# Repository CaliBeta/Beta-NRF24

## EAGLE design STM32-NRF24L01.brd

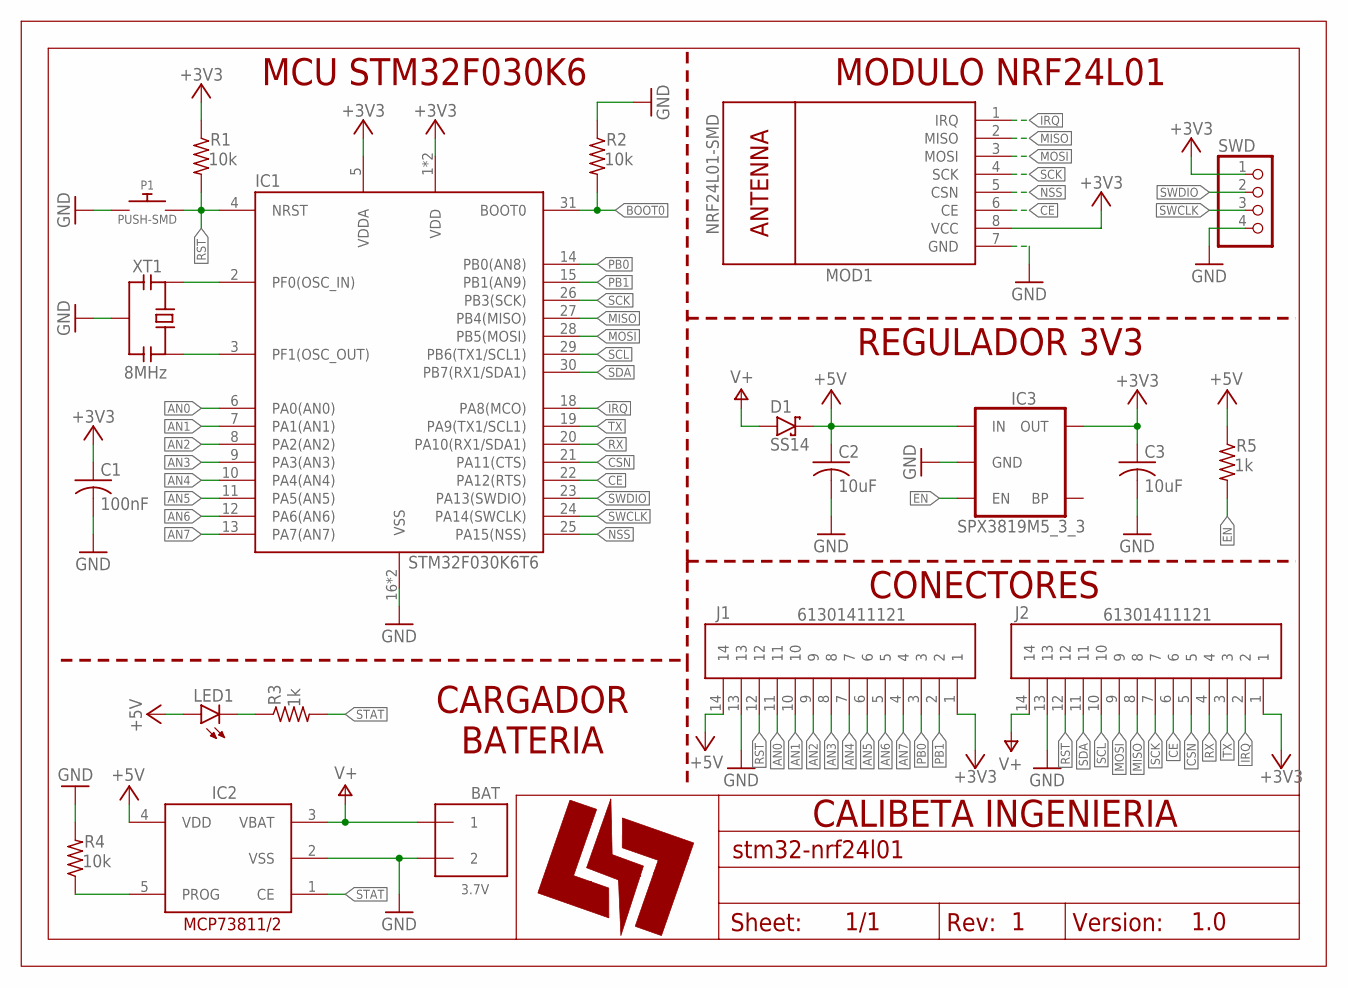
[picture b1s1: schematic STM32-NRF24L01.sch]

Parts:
BAT: 3.7V; S2B-PH-SM4
C1: 100nF; C0805
C2, C3: 10uF; C0805
D1: SS14; DO-214AC
IC1: STM32F030K6T6; LQFP32
IC2: MCP73811/2; SOT23-5L
IC3: SPX3819M5_3_3; SOT23-5
J1, J2: 61301411121
LED1: LED-ROJO0805; LED0805-ROJO
MOD1: NRF24L01-SMD
P1: PUSH-SMD; ST-SMD-6X3.5MM
R1, R2, R4: 10k; R0805
R3, R5: 1k; R0805
SWD: PINHD-1X4/90; 1X04/90
U$1: A5_H-LOGO; LOGO-10MM
XT1: 8MHz; 3-SMD

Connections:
+3V3: C1.1, C3.1, IC1.1 (VDD), IC1.5 (VDDA), IC1.17 (VDD), IC3.5 (OUT), J1.1, J2.1, MOD1.8 (VCC), R1.1, SWD.1
+5V: C2.1, D1.K, IC2.4 (VDD), IC3.1 (IN), J1.14, LED1.A, R5.1
AN0: IC1.6 (PA0(AN0)), J1.11
AN1: IC1.7 (PA1(AN1)), J1.10
AN2: IC1.8 (PA2(AN2)), J1.9
AN3: IC1.9 (PA3(AN3)), J1.8
AN4: IC1.10 (PA4(AN4)), J1.7
AN5: IC1.11 (PA5(AN5)), J1.6
AN6: IC1.12 (PA6(AN6)), J1.5
AN7: IC1.13 (PA7(AN7)), J1.4
BOOT0: IC1.31 (BOOT0), R2.2
CE: IC1.22 (PA12(RTS)), J2.6, MOD1.6 (CE)
CSN: IC1.21 (PA11(CTS)), J2.5
EN: IC3.3 (EN), R5.2
GND: BAT.2, C1.2, C2.2, C3.2, IC1.16 (VSS), IC1.32 (VSS), IC2.2 (VSS), IC3.2 (GND), J1.13, J2.13, MOD1.7 (GND), P1.1, R2.1, R4.2, SWD.4, XT1.2 (GND)
IRQ: IC1.18 (PA8(MCO)), J2.2, MOD1.1 (IRQ)
MISO: IC1.27 (PB4(MISO)), J2.8, MOD1.2 (MISO)
MOSI: IC1.28 (PB5(MOSI)), J2.9, MOD1.3 (MOSI)
unnamed: IC1.2 (PF0(OSC_IN)), XT1.1 (X1)
unnamed: IC1.3 (PF1(OSC_OUT)), XT1.3 (X2)
unnamed: LED1.C, R3.1
unnamed: IC2.5 (PROG), R4.1
NSS: IC1.25 (PA15(NSS)), MOD1.5 (CSN)
PB0: IC1.14 (PB0(AN8)), J1.3
PB1: IC1.15 (PB1(AN9)), J1.2
RST: IC1.4 (NRST), J1.12, J2.12, P1.2, R1.2
RX: IC1.20 (PA10(RX1/SDA1)), J2.4
SCK: IC1.26 (PB3(SCK)), J2.7, MOD1.4 (SCK)
SCL: IC1.29 (PB6(TX1/SCL1)), J2.10
SDA: IC1.30 (PB7(RX1/SDA1)), J2.11
STAT: IC2.1 (CE), R3.2
SWCLK: IC1.24 (PA14(SWCLK)), SWD.3
SWDIO: IC1.23 (PA13(SWDIO)), SWD.2
TX: IC1.19 (PA9(TX1/SCL1)), J2.3
V+: BAT.1, D1.A, IC2.3 (VBAT), J2.14

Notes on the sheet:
MCU STM32F030K6
MODULO NRF24L01
CARGADOR BATERIA
REGULADOR 3V3
CONECTORES
1.0

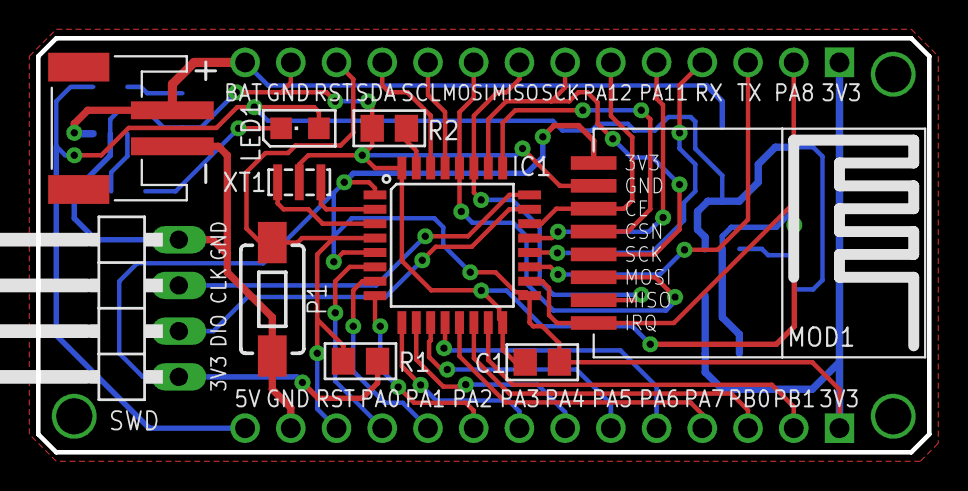
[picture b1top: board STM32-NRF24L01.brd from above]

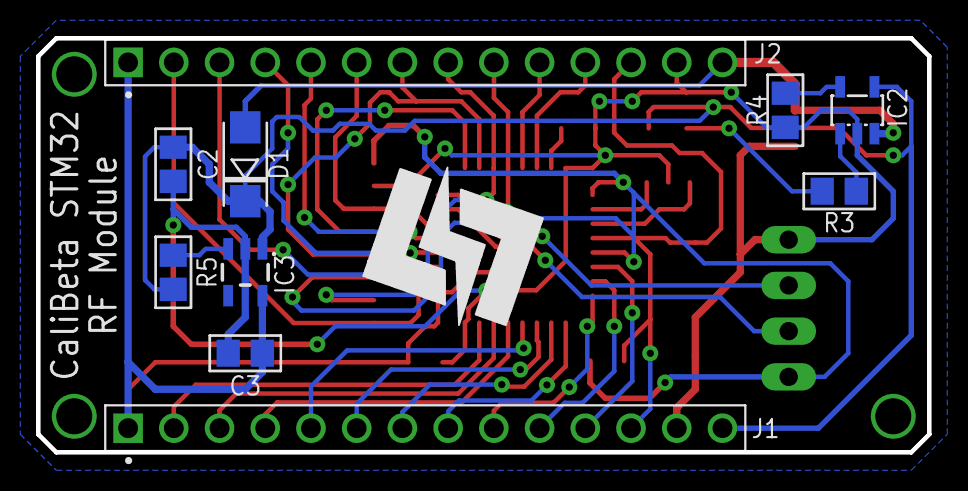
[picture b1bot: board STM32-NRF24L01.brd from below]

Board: 2 copper layers, 49.5 x 23.0 mm, 21 parts (11 on the bottom side), 35 nets.

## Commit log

2021-06-09 Commit inicial, Add STM32F030K6 y NRF24L01
2021-06-09 Add conectores y circuiteria basica para el STM32
2021-06-09 Add cargador de bateria
2021-06-09 Add Regulador 3V3
2021-06-10 Terminado SCH, Inicio BRD
2021-06-10 Posicionado componentes, inicio ruteo
2021-06-10 Ruteo al 50%
2021-06-10 Terminado Ruteo
2021-06-10 Generado Gerber, imagenes y BOMLIST

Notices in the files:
parts and their libraries:
SparkFun-IC-Power: Licensing: Creative Commons ShareAlike 4.0 International - https://creativecommons.org/licenses/by-sa/4.0
